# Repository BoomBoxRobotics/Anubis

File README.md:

# Anubis RC Controller Daughterboard

**A compact open-hardware support board for a DIY ESP32-S3 RC transmitter.**

Anubis is an open hardware and open firmware RC controller project built around accessible DIY parts, modern radio-control features, and a design that builders can understand, repair, modify, and improve.

This repository contains the custom daughterboard for the Anubis controller. It sits under a Hosyond 2.8 inch ESP32-S3 display board and turns the early wiring-heavy prototype into a cleaner, more repeatable hardware platform.

## Mission

The goal is simple: make a capable, repairable, hackable transmitter that is not locked behind a black box.

The first Anubis prototype used off-the-shelf modules wired together by hand: display board, power switches, regulators, analog input boards, GPIO expanders, gimbal connectors, and radio wiring. That is a great way to prove an idea, but it gets messy fast. This daughterboard pulls those support circuits onto a purpose-built PCB while leaving the Hosyond ESP32-S3 board as the main brain, display, touch interface, and firmware target.

Anubis is meant for experimentation as much as use. Builders should be able to change pin mappings, adapt connectors, swap radio hardware, and tune the firmware for their own transmitter layout.

## At A Glance

| Area | Current Direction |
| --- | --- |
| Main controller | Hosyond 2.8 inch ESP32-S3 display/dev board |
| Battery system | 2S LiPo or two 18650 cells as a 2S pack |
| Charging input | USB-C 5 V input, 500 mA to 1.5 A charge target |
| Switched outputs | `+5V_SW` and `+3V3_SW` accessory rails |
| Analog inputs | Two onboard ADS1115 ADCs, up to 8 analog channels |
| GPIO expansion | MCP23017 16-bit I2C GPIO expander |
| Radio paths | ELRS/CRSF over UART and optional ESP-NOW |
| Assembly goal | As much JLCPCB assembly as practical |
| Project status | Prototype hardware, ready for assembled-board validation |

## Core Design Goals

- Use common, hobby-accessible parts where possible.
- Keep the project open enough for community modification.
- Support modern RC workflows such as ELRS and ESP-NOW.
- Reduce hand wiring compared with the early prototype.
- Make the board practical for JLCPCB assembly.
- Keep external accessory power switchable from firmware.
- Leave room for manual wiring where real-world modules and harnesses vary.

## Hardware Overview

The daughterboard adds the support electronics around the Hosyond ESP32-S3 board:

- USB-C 5 V input for charging and power input.
- Standard 2S LiPo balance connector for the battery pack.
- Support for a 2S LiPo pack or two 18650 cells configured as a 2S pack.
- 2S battery gauge/protection circuitry based around `BQ28Z610DRZR-R1`.
- R14 high-side protection path using two JLC-available `CSD18502Q5B` N-FETs, with the charger and buck regulators fed from protected `BAT_SYS`.
- Switched 5 V rail for UART/ELRS-side accessories.
- Switched 3.3 V rail for I2C, analog, and low-voltage peripherals.
- Two Pololu mini pushbutton power switch modules for rail control.
- Two onboard ADS1115 ADC circuits for up to eight analog inputs.
- One onboard MCP23017 GPIO expander for buttons and digital expansion.
- JST and pin-header breakouts for UART, I2C, GPIO, gimbals, and accessories.
- ESD protection for external signal connections.
- Ground plane and wider routing rules for higher-current power paths.

## Power Rails

| Rail | Intended Use | Approximate Max Current |
| --- | --- | --- |
| USB-C input | 5 V charge/input source | 500 mA to 1.5 A charge target |
| `+5V_SW` | ELRS/UART-side accessory power | about 1 A |
| `+3V3_SW` | I2C, ADCs, MCP23017, gimbals, sensors | about 500 mA |

The switched rails are controlled through the two Pololu #2808 mini pushbutton power switch modules. The ESP32-S3 can shut down attached devices without relying on the attached devices to behave nicely.

## Firmware Map

The main Anubis firmware runs on the Hosyond ESP32-S3 board. Current daughterboard-aware firmware support includes:

- Touchscreen UI for transmitter settings.
- Model storage and configuration.
- Stick calibration.
- Expo, rates, trims, endpoints, failsafe, and mixing.
- ELRS/CRSF support over UART.
- ESP-NOW transmitter support.
- Dual ADS1115 support for onboard analog inputs at `0x48` and `0x49`.
- MCP23017 GPIO expander support at `0x20`.
- Battery monitoring and deep-sleep behavior.

### Pin Assignments

| Function | ESP32-S3 Pin |
| --- | --- |
| I2C SDA | GPIO16 |
| I2C SCL | GPIO15 |
| ELRS/UART TX | GPIO44 |
| ELRS/UART RX | GPIO43 |
| Battery ADC | GPIO9 |
| 5 V rail switch control | GPIO2 |
| 3.3 V rail switch control | GPIO3 |
| Deep-sleep/wake button sense | GPIO14 |
| Deep-sleep/wake button reference | GPIO21 |

GPIO2 and GPIO3 control the two Pololu rail-switch modules. GPIO14 and GPIO21 route to the two-pin deep-sleep/wake pushbutton header. UART-to-ELRS wiring can still be crossed manually if a specific module harness expects the opposite order.

### I2C Devices

| Device | Address | Role |
| --- | --- | --- |
| ADS1115 primary | `0x48` | Four gimbal/stick analog axes |
| ADS1115 auxiliary | `0x49` | Spare analog inputs |
| MCP23017 | `0x20` | GPIO expansion and active-low button/switch inputs |
| BQ25887 charger | `0x6B` | 2S charger status and pack voltage reporting |

## Control Hardware

The controller is designed around parts that are easy for hobby builders to source or substitute:

- Hosyond 2.8 inch ESP32-S3 display board as the main controller.
- RadioMaster Pocket/Zorro X5-style gimbals.
- ELRS module support through UART/CRSF.
- Optional ESP-NOW receiver support for WiFi-equipped ESP32 receivers.
- D-pad/button input through the MCP23017 GPIO expander.
- Auxiliary analog inputs through the ADS1115 circuits.

The mechanical layout fits around the Hosyond board and controller shell constraints. The Hosyond board sits above the daughterboard on standoffs, with the daughterboard occupying the surrounding and lower internal space.

## Repository Contents

| Path | Purpose |
| --- | --- |
| `Daughterboard.kicad_pro` | KiCad project file |
| `Daughterboard.kicad_sch` | Main schematic |
| `Daughterboard.kicad_pcb` | PCB layout |
| `Daughterboard.kicad_sym` | Project symbols |
| `Daughterboard.pretty/` | Custom KiCad footprints |
| `Daughterboard.net` | Exported netlist |
| `Daughterboard_pcb_bom.csv` | Human-readable PCB BOM |
| `Daughterboard_current_jlc_part_audit.csv` | JLC part audit/reference |
| `fabrication/` | Fabrication and assembly outputs |
| `daughterboard2.dxf` | Board outline reference |
| `Daughterboardv2.step` | Mechanical board reference |
| `PROJECT_CONTEXT.md` | Detailed working context for future development |

Current fabrication package:

```text
fabrication/jlcpcb_2026-07-10_r14.zip
```

Assembly files are included under:

```text
fabrication/jlcpcb_2026-07-10_r14/assembly/
```

## Manufacturing Notes

The board is being prepared for JLCPCB assembly with as many populated parts as practical. The Pololu mini pushbutton power switch modules are treated as separately installed modules. Some through-hole headers may also be hand-installed unless through-hole assembly is explicitly ordered.

Before ordering boards, always check:

- KiCad ERC and DRC reports.
- Copper clearance and board-edge clearance.
- Unrouted nets.
- Connector orientation.
- IC pin 1 orientation.
- JLCPCB part availability.
- BOM and CPL alignment in the JLCPCB preview.

Known current status from the active R14 working files:

- ERC reports no errors or warnings.
- Q1/Q2 are now JLC-available `CSD18502Q5B` FETs using project-local TI DNK/VSON-CLIP footprints.
- The R14 topology audit passes: USB-C ground, charger/system bus, high-side protection FETs, current-sense resistor, and SRP/SRN polarity all match the corrected battery-protection intent.
- The PCB has been rerouted after the Q1/Q2 footprint swap and the GND zone has been refilled.
- DRC currently reports 40 known non-connectivity items and 0 unconnected pads/items.
- JLC assembly still needs confirmed selections for `R49` and `R50`.
- Silkscreen warnings should not normally prevent fabrication.
- Copper, drill, outline, missing-net, and footprint-orientation issues should be treated as critical.

## Battery And Power Safety

This board works with lithium battery packs and charging/protection circuitry. Mistakes can damage hardware or create a safety hazard.

Do not assume a PCB revision is safe just because the schematic opens or the Gerbers generate. Review the battery path, charger configuration, protection FETs, current limits, connector polarity, and pack wiring before connecting real cells.

Use protected cells or a known-good 2S pack during testing. Current-limit the first power-up and verify rails with a meter before plugging in the Hosyond board or radio hardware.

## Project Status

This hardware is still a prototype until assembled boards are tested.

Open work includes:

- Validate the physical PCB after manufacturing.
- Confirm all connector orientations in the assembled board.
- Test the updated firmware GPIO assignments against the first assembled daughterboard.
- Verify 2S battery reporting and charger/fuel-gauge behavior on hardware.
- Confirm the auxiliary ADS1115 inputs and MCP23017 pads behave as expected with real devices attached.
- Test ELRS and ESP-NOW behavior in the finished controller.
- Document assembly steps after the first successful build.

## Contributing

Anubis is meant to be community driven. Contributions are welcome in the form of firmware changes, PCB review, mechanical improvements, documentation, testing notes, alternate part suggestions, and build reports.

If you change the hardware, include enough context for another builder to understand why the change was made. If you change the firmware, document the pin assumptions and hardware revision you tested against.

## Companion Project

The firmware and receiver-side code for the broader Anubis controller project are hosted with the main project:

```text
https://github.com/BoomBoxRobotics/Anubis
```

This daughterboard is one hardware path toward that larger goal: a capable open source RC controller that builders can actually understand, repair, and make their own.

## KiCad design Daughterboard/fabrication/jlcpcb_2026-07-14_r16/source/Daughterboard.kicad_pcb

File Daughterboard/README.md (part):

# Anubis RC Controller Daughterboard

**A compact open-hardware support board for a DIY ESP32-S3 RC transmitter.**

Anubis is an open hardware and open firmware RC controller project built around accessible DIY parts, modern radio-control features, and a design that builders can understand, repair, modify, and improve.

This repository contains the custom daughterboard for the Anubis controller. It sits under a Hosyond 2.8 inch ESP32-S3 display board and turns the early wiring-heavy prototype into a cleaner, more repeatable hardware platform.

## Mission

The goal is simple: make a capable, repairable, hackable transmitter that is not locked behind a black box.

The first Anubis prototype used off-the-shelf modules wired together by hand: display board, power switches, regulators, analog input boards, GPIO expanders, gimbal connectors, and radio wiring. That is a great way to prove an idea, but it gets messy fast. This daughterboard pulls those support circuits onto a purpose-built PCB while leaving the Hosyond ESP32-S3 board as the main brain, display, touch interface, and firmware target.

Anubis is meant for experimentation as much as use. Builders should be able to change pin mappings, adapt connectors, swap radio hardware, and tune the firmware for their own transmitter layout.

## At A Glance

| Area | Current Direction |
| --- | --- |
| Main controller | Hosyond 2.8 inch ESP32-S3 display/dev board |
| Battery system | 2S LiPo or two 18650 cells as a 2S pack |
| Charging input | USB-C 5 V input, 500 mA to 1.5 A charge target |
| Switched outputs | `+5V_SW` and `+3V3_SW` accessory rails |
| Analog inputs | Two onboard ADS1115 ADCs, up to 8 analog channels |
| GPIO expansion | MCP23017 16-bit I2C GPIO expander |
| Radio paths | ELRS/CRSF over UART and optional ESP-NOW |
| Assembly goal | As much JLCPCB assembly as practical |
| Project status | Prototype hardware, ready for assembled-board validation |

## Core Design Goals

- Use common, hobby-accessible parts where possible.
- Keep the project open enough for community modification.
- Support modern RC workflows such as ELRS and ESP-NOW.
- Reduce hand wiring compared with the early prototype.
- Make the board practical for JLCPCB assembly.
- Keep external accessory power switchable from firmware.
- Leave room for manual wiring where real-world modules and harnesses vary.

## Hardware Overview

The daughterboard adds the support electronics around the Hosyond ESP32-S3 board:

- USB-C 5 V input for charging and power input.
- Standard 2S LiPo balance connector for the battery pack.
- Support for a 2S LiPo pack or two 18650 cells configured as a 2S pack.
- 2S battery gauge/protection circuitry based around `BQ28Z610DRZR-R1`.
- R14 high-side protection path using two JLC-available `CSD18502Q5B` N-FETs, with the charger and buck regulators fed from protected `BAT_SYS`.
- Switched 5 V rail for UART/ELRS-side accessories.
- Switched 3.3 V rail for I2C, analog, and low-voltage peripherals.
- Two Pololu mini pushbutton power switch modules for rail control.
- Two onboard ADS1115 ADC circuits for up to eight analog inputs.
- One onboard MCP23017 GPIO expander for buttons and digital expansion.
- JST and pin-header breakouts for UART, I2C, GPIO, gimbals, and accessories.
- ESD protection for external signal connections.
- Ground plane and wider routing rules for higher-current power paths.

## Power Rails

| Rail | Intended Use | Approximate Max Current |
| --- | --- | --- |
| USB-C input | 5 V charge/input source | 500 mA to 1.5 A charge target |
| `+5V_SW` | ELRS/UART-side accessory power | about 1 A |
| `+3V3_SW` | I2C, ADCs, MCP23017, gimbals, sensors | about 500 mA |

The switched rails are controlled through the two Pololu #2808 mini pushbutton power switch modules. The ESP32-S3 can shut down attached devices without relying on the attached devices to behave nicely.

## Firmware Map

The main Anubis firmware runs on the Hosyond ESP32-S3 board. Current daughterboard-aware firmware support includes:

- Touchscreen UI for transmitter settings.
- Model storage and configuration.
- Stick calibration.
- Expo, rates, trims, endpoints, failsafe, and mixing.
- ELRS/CRSF support over UART.
- ESP-NOW transmitter support.
- Dual ADS1115 support for onboard analog inputs at `0x48` and `0x49`.
- MCP23017 GPIO expander support at `0x20`.
- Battery monitoring and deep-sleep behavior.

### Pin Assignments

| Function | ESP32-S3 Pin |
| --- | --- |
| I2C SDA | GPIO16 |
| I2C SCL | GPIO15 |
| ELRS/UART TX | GPIO44 |
| ELRS/UART RX | GPIO43 |
| Battery ADC | GPIO9 |
| 5 V rail switch control | GPIO2 |
| 3.3 V rail switch control | GPIO3 |
| Deep-sleep/wake button sense | GPIO14 |
| Deep-sleep/wake button reference | GPIO21 |

GPIO2 and GPIO3 control the two Pololu rail-switch modules. GPIO14 and GPIO21 route to the two-pin deep-sleep/wake pushbutton header. UART-to-ELRS wiring can still be crossed manually if a specific module harness expects the opposite order.

### I2C Devices

| Device | Address | Role |
| --- | --- | --- |
| ADS1115 primary | `0x48` | Four gimbal/stick analog axes |
| ADS1115 auxiliary | `0x49` | Spare analog inputs |
| MCP23017 | `0x20` | GPIO expansion and active-low button/switch inputs |
| BQ25887 charger | `0x6B` | 2S charger status and pack voltage reporting |

## Board Connection Reference

The following tables describe the designators and nets on the R14 PCB. Pin numbers are the KiCad footprint pin numbers and should be checked against connector orientation and pin-1 markings before making a cable.

### Electrical Test Pads

| Pad | Net | Signal source or intended measurement |
| --- | --- | --- |
| `TP1` | `USB_VBUS` | USB-C `J1` VBUS, before input fuse `F1` |
| `TP2` | `CHG_IN` | Fused USB input after `F1`; charger `U1` pin 23 |
| `TP3` | `BAT_SYS` | Protected battery/system bus feeding charger `U1` BAT pins and the 5 V/3.3 V regulators |
| `TP4` | `CELL_MID` | 2S pack midpoint from `J7` pin 2; charger `U1` pin 9 sense connection |
| `TP5` | `BAT_SYS` | Second protected battery/system-bus test point; electrically the same as `TP3` |
| `TP6` | `+5V` | Unswitched 5 V regulator output after `L1`, before Pololu switch `SW1` |
| `TP7` | `+3V3` | Unswitched 3.3 V regulator output after `L2`, before Pololu switch `SW2` |
| `TP9` | `+3V3_SW` | Switched 3.3 V output from `SW2` |
| `TP10` | `CHG_STAT` | Charger `U1` pin 2 charge-status output; also drives status LED `D2` |
| `TP11` | `PG_STAT` | Charger `U1` pin 1 power-good output; also drives status LED `D3` |
| `TP12` | `BATT_RAW_N` | Raw pack negative from `J7` pin 1, on the battery side of current-sense resistor `R46` |
| `TP13` | `BATT_RAW_P` | Raw pack positive from `J7` pin 3 |
| `TP14` | `GND` | System ground, on the system side of current-sense resistor `R46` |
| `TP15` | `AIN4` | Auxiliary ADC `U6` (`0x49`) AIN0, pin 4 |
| `TP16` | `AIN5` | Auxiliary ADC `U6` (`0x49`) AIN1, pin 5 |
| `TP17` | `AIN6` | Auxiliary ADC `U6` (`0x49`) AIN2, pin 6 |
| `TP18` | `AIN7` | Auxiliary ADC `U6` (`0x49`) AIN3, pin 7 |

`TP8` is not fitted on the R14 PCB. Use `J30` or `J4` pin 1 to access `+5V_SW`. Also note that `BATT_RAW_N` and `GND` are separated by the 2 mOhm current-sense resistor; do not treat `TP12` and `TP14` as interchangeable measurement points.

### Hosyond Manual Solder Pads

These pads replace the original `J3` connector so individual wires from the Hosyond board can be soldered directly to the daughterboard.

| Pad | Net | Hosyond/source mapping |
| --- | --- | --- |
| `J30` | `+5V_SW` | Switched 5 V output from `SW1`; also available at `J4` pin 1 |
| `J31` | `UART_TX` | Hosyond ESP32-S3 GPIO44; routed to `J4` pin 3 |
| `J32` | `UART_RX` | Hosyond ESP32-S3 GPIO43; routed to `J4` pin 4 |
| `J33` | `I2C_SDA` | Hosyond ESP32-S3 GPIO16; shared daughterboard I2C data bus |
| `J34` | `I2C_SCL` | Hosyond ESP32-S3 GPIO15; shared daughterboard I2C clock bus |
| `J35` | `GPIO2` | Hosyond ESP32-S3 GPIO2; drives `SW1` 5 V control through `R17` |
| `J36` | `GPIO3` | Hosyond ESP32-S3 GPIO3; drives `SW2` 3.3 V control through `R18` |
| `J37` | `GPIO14` | Hosyond ESP32-S3 GPIO14; routed to wake-button header `J6` pin 1 |
| `J38` | `GPIO21` | Hosyond ESP32-S3 GPIO21; routed to wake-button header `J6` pin 2 |
| `J39` | `GND` | Daughterboard system ground |

### MCP23017 Manual Solder Pads

The `EXP_*` GPIO pads are on the protected external side of a 100 ohm series resistor and an ESD array. `U7` is the MCP23017 at I2C address `0x20`.

| Pad | Net | Source |
| --- | --- | --- |
| `J91` | `EXP_GPA0` | `U7` GPA0 pin 21 through `R23`; ESD `D4` |
| `J92` | `EXP_GPA1` | `U7` GPA1 pin 22 through `R24`; ESD `D4` |
| `J93` | `EXP_GPA2` | `U7` GPA2 pin 23 through `R25`; ESD `D4` |
| `J94` | `EXP_GPA3` | `U7` GPA3 pin 24 through `R26`; ESD `D4` |
| `J95` | `EXP_GPA4` | `U7` GPA4 pin 25 through `R27`; ESD `D5` |
| `J96` | `EXP_GPA5` | `U7` GPA5 pin 26 through `R28`; ESD `D5` |
| `J97` | `EXP_GPA6` | `U7` GPA6 pin 27 through `R29`; ESD `D5` |
| `J98` | `EXP_GPA7` | `U7` GPA7 pin 28 through `R30`; ESD `D5` |
| `J99` | `EXP_GPB0` | `U7` GPB0 pin 1 through `R31`; ESD `D6` |
| `J910` | `EXP_GPB1` | `U7` GPB1 pin 2 through `R32`; ESD `D6` |
| `J911` | `EXP_GPB2` | `U7` GPB2 pin 3 through `R33`; ESD `D6` |
| `J912` | `EXP_GPB3` | `U7` GPB3 pin 4 through `R34`; ESD `D6` |
| `J913` | `EXP_GPB4` | `U7` GPB4 pin 5 through `R35`; ESD `D7` |
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
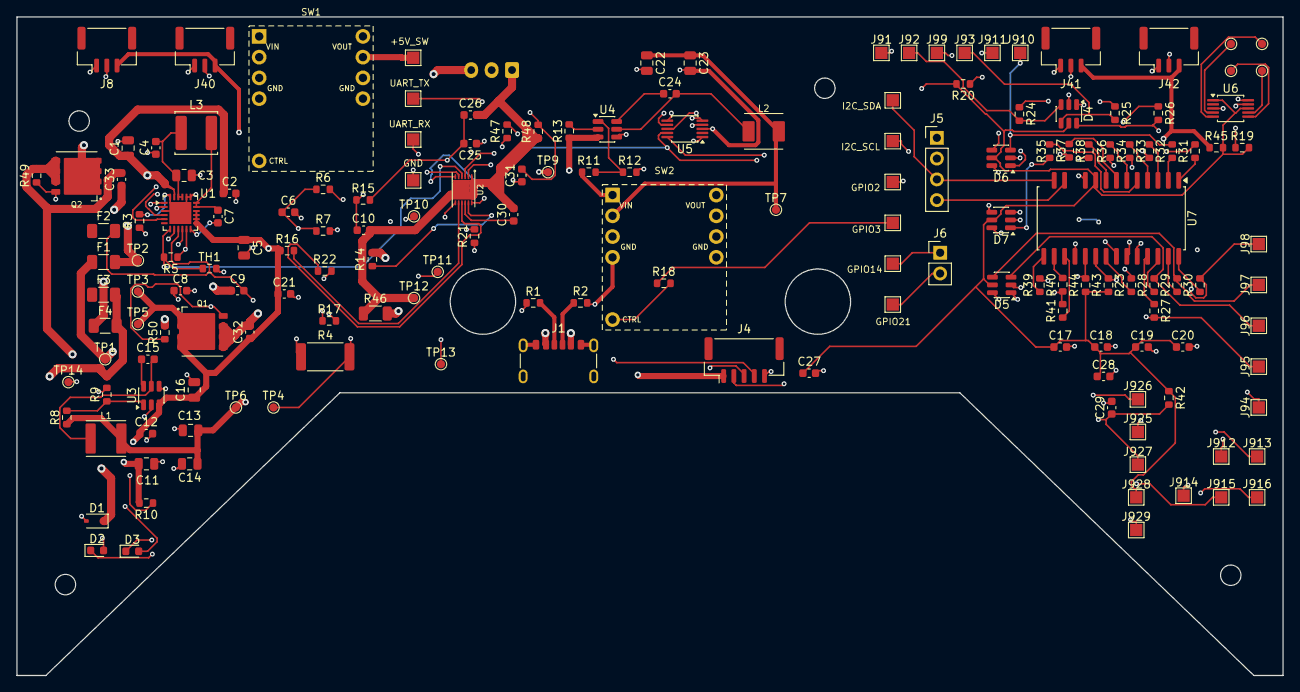
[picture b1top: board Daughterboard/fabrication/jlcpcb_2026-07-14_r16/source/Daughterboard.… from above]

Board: 4 copper layers, 155.0 x 80.6 mm, 166 parts (0 on the bottom side), 101 nets.

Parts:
C1: 10uF 10V X5R; C_0805_2012Metric
C2, C17, C19, C27, C29: 100nF 10V X7R; C_0603_1608Metric
C3, C5, C13, C14, C22, C23: 22uF 16V X5R; C_0805_2012Metric
C4, C7, C9, C10, C12, C15, C21, C24, C25, C26, C31: 100nF 16V X7R; C_0603_1608Metric
C6: 4.7uF 6.3V X5R; C_0603_1608Metric
C8: 100nF 10V X7R DNP; C_0603_1608Metric
C11, C16: 10uF 16V X5R; C_0805_2012Metric
C18, C20, C28: 1uF 10V X5R; C_0603_1608Metric
C30: 2.2uF 10V X5R; C_0603_1608Metric
C32, C33: 100nF 25V X7R; C_0603_1608Metric
D1: PESD5V0S1BA 5V VBUS TVS; D_SOD-323
D2: LED green; LED_0603_1608Metric
D3: LED blue; LED_0603_1608Metric
D4, D5, D6, D7: SRV05-4.TCT / C13612 4ch ESD; SOT-23-6
F1: BSMD1206-200-16V 2A hold polyfuse; Fuse_1206_3216Metric
F2: BSMD1206-200-16V cell1 PTC; Fuse_1206_3216Metric
F3: BSMD1206-200-16V cell2 PTC; Fuse_1206_3216Metric
F4: BSMD1206-200-16V system fuse; Fuse_1206_3216Metric
J1: USB-C 5V Sink; USB_C_Receptacle_GCT_USB4125-xx-x_6P_TopMnt_Horizontal
J4: BM05B-GHS-TBT UART JST-GH top-entry 1.25mm; JST_GH_BM05B-GHS-TBT_1x05-1MP_P1.25mm_Vertical
J5: I2C 2.54mm through-hole male header; PinHeader_1x04_P2.54mm_Vertical
J6: Deep sleep 2.54mm through-hole header; PinHeader_1x02_P2.54mm_Vertical
J7: 2S balance input JST-XH side-entry; JST_XH_S3B-XH-A_1x03_P2.50mm_Horizontal
J8: Left gimbal A JST-GH 1.25mm; JST_GH_BM03B-GHS-TBT_1x03-1MP_P1.25mm_Vertical
J30: J3P Hosyond +5V_SW solder pad; TestPoint_Pad_1.5x1.5mm
J31: J3A Hosyond UART_TX solder pad; TestPoint_Pad_1.5x1.5mm
J32: J3B Hosyond UART_RX solder pad; TestPoint_Pad_1.5x1.5mm
J33: J3C Hosyond I2C_SDA solder pad; TestPoint_Pad_1.5x1.5mm
J34: J3D Hosyond I2C_SCL solder pad; TestPoint_Pad_1.5x1.5mm
J35: J3E Hosyond GPIO2 solder pad; TestPoint_Pad_1.5x1.5mm
J36: J3F Hosyond GPIO3 solder pad; TestPoint_Pad_1.5x1.5mm
J37: J3G Hosyond GPIO14 solder pad; TestPoint_Pad_1.5x1.5mm
J38: J3H Hosyond GPIO21 solder pad; TestPoint_Pad_1.5x1.5mm
J39: J3I Hosyond GND solder pad; TestPoint_Pad_1.5x1.5mm
J40: Left gimbal B JST-GH 1.25mm; JST_GH_BM03B-GHS-TBT_1x03-1MP_P1.25mm_Vertical
J41: Right gimbal A JST-GH 1.25mm; JST_GH_BM03B-GHS-TBT_1x03-1MP_P1.25mm_Vertical
J42: Right gimbal B JST-GH 1.25mm; JST_GH_BM03B-GHS-TBT_1x03-1MP_P1.25mm_Vertical
J91: MCP23017 GPA0 solder pad; TestPoint_Pad_1.5x1.5mm
J92: MCP23017 GPA1 solder pad; TestPoint_Pad_1.5x1.5mm
J93: MCP23017 GPA2 solder pad; TestPoint_Pad_1.5x1.5mm
J94: MCP23017 GPA3 solder pad; TestPoint_Pad_1.5x1.5mm
J95: MCP23017 GPA4 solder pad; TestPoint_Pad_1.5x1.5mm
J96: MCP23017 GPA5 solder pad; TestPoint_Pad_1.5x1.5mm
J97: MCP23017 GPA6 solder pad; TestPoint_Pad_1.5x1.5mm
J98: MCP23017 GPA7 solder pad; TestPoint_Pad_1.5x1.5mm
J99: MCP23017 GPB0 solder pad; TestPoint_Pad_1.5x1.5mm
J910: MCP23017 GPB1 solder pad; TestPoint_Pad_1.5x1.5mm
J911: MCP23017 GPB2 solder pad; TestPoint_Pad_1.5x1.5mm
J912: MCP23017 GPB3 solder pad; TestPoint_Pad_1.5x1.5mm
J913: MCP23017 GPB4 solder pad; TestPoint_Pad_1.5x1.5mm
J914: MCP23017 GPB5 solder pad; TestPoint_Pad_1.5x1.5mm
J915: MCP23017 GPB6 solder pad; TestPoint_Pad_1.5x1.5mm
J916: MCP23017 GPB7 solder pad; TestPoint_Pad_1.5x1.5mm
J925: MCP23017 INTA solder pad; TestPoint_Pad_1.5x1.5mm
J926: MCP23017 INTB solder pad; TestPoint_Pad_1.5x1.5mm
J927: MCP23017 RESET solder pad; TestPoint_Pad_1.5x1.5mm
J928: MCP23017 +3V3_SW solder pad; TestPoint_Pad_1.5x1.5mm
J929: MCP23017 GND solder pad; TestPoint_Pad_1.5x1.5mm
L1: 4.7uH >=3A sat; CENKER_CKST0402_4.6x4.1mm
L2: 4.7uH >=2A sat; KOHERelec_MDA4020_4.45x4.1mm
L3: ANR5040T1R0M 1uH; L_APV_ANR5040
Q1: CSD18502Q5B charge FET; CSD18502Q5B_DNK0008A_VSON-CLIP_5x6mm
Q2: CSD18502Q5B discharge FET; CSD18502Q5B_DNK0008A_VSON-CLIP_5x6mm
R1, R2: 5.1k 1%; R_0603_1608Metric
R3: 806R 1% ILIM; R_0603_1608Metric
R4: 43R 1W CBSET; R_2512_6332Metric
R5: 10k 1%; R_0603_1608Metric
R6, R7: 2.2k; R_0603_1608Metric
R8: 523k 1%; R_0603_1608Metric
R9, R12: 100k 1%; R_0603_1608Metric
R10, R13: 100k; R_0603_1608Metric
R11: 316k 1%; R_0603_1608Metric
R14, R15: 470R 1%; R_0603_1608Metric
R16, R21, R22, R23, R24, R25, R26, R27, R28, R29, R30, R31, R32, R33, R34, R35, R36, R37, R38, R47, R48: 100R; R_0603_1608Metric
R17, R18: 330R; R_0603_1608Metric
R19, R20: 4.7k; R_0603_1608Metric
R39, R40, R41, R45: 0R; R_0603_1608Metric
R42, R43, R44: 10k; R_0603_1608Metric
R46: 2mR 1% 50ppm; R_1206_3216Metric
R49, R50: 10M; R_0603_1608Metric
SW1: Pololu #2808 5V switch; Pololu_2808_Raised_Header
SW2: Pololu #2808 3V3 switch; Pololu_2808_Raised_Header
TH1: NCP18XH103F03RB 10k NTC; R_0603_1608Metric
TP1: USB_VBUS test pad; TestPoint_Pad_D1.0mm
TP2: CHG_IN test pad; TestPoint_Pad_D1.0mm
TP3, TP5: BAT_SYS test pad; TestPoint_Pad_D1.0mm
TP4: CELL_MID test pad; TestPoint_Pad_D1.0mm
TP6: +5V test pad; TestPoint_Pad_D1.0mm
TP7: +3V3 test pad; TestPoint_Pad_D1.0mm
TP9: +3V3_SW test pad; TestPoint_Pad_D1.0mm
TP10: CHG_STAT test pad; TestPoint_Pad_D1.0mm
TP11: PG_STAT test pad; TestPoint_Pad_D1.0mm
TP12: BATT_RAW_N test pad; TestPoint_Pad_D1.0mm
TP13: BATT_RAW_P test pad; TestPoint_Pad_D1.0mm
TP14: GND test pad; TestPoint_Pad_D1.0mm
TP15: AIN4 test pad; TestPoint_Pad_D1.0mm
TP16: AIN5 test pad; TestPoint_Pad_D1.0mm
TP17: AIN6 test pad; TestPoint_Pad_D1.0mm
TP18: AIN7 test pad; TestPoint_Pad_D1.0mm
U1: BQ25887RGER 2S charger; Texas_RGE0024H_VQFN-24-1EP_4x4mm_P0.5mm_EP2.7x2.7mm
U2: BQ28Z610DRZR-R1; TI_DRZ0012A_VSON-12_4x2.5mm_P0.4mm
U3: AP63200WU-7 5V Buck; TSOT-23-6
U4: AP63200WU-7 3V3 Buck; TSOT-23-6
U5: ADS1115IDGSR 0x48; TSSOP-10_3x3mm_P0.5mm
U6: ADS1115IDGSR 0x49; TSSOP-10_3x3mm_P0.5mm
U7: MCP23017-E/SO; SOIC-28W_7.5x17.9mm_P1.27mm_NoPads11_14

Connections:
+3V3: C22.1, C23.1, L2.2, R11.1, SW2.1, TP7.1
+3V3_SW: J5.1, J8.3, J40.3, J41.3, J42.3, R45.1, SW2.2, TP9.1
+3V3_SW_LOGIC: C17.1, C18.1, C19.1, C20.1, C27.1, C28.1, D4.5, D5.5, D6.5, D7.5, J928.1, R19.2, R20.2, R42.1, R43.1, R44.1, R45.2, U5.8, U6.1, U6.8, U7.9
+5V: C13.1, C14.1, L1.2, R8.1, SW1.1, TP6.1
+5V_SW: J4.1, J30.1, SW1.2
AIN0: J8.2, U5.4
AIN1: J40.2, U5.5
AIN2: J41.2, U5.6
AIN3: J42.2, U5.7
AIN4: TP15.1, U6.4
AIN5: TP16.1, U6.5
AIN6: TP17.1, U6.6
AIN7: TP18.1, U6.7
BATT_RAW_N: C10.2, C26.2, C30.2, J7.1, R46.1, R48.1, TP12.1, U2.1, U2.13
BATT_RAW_P: C9.1, F3.2, F4.2, J7.3, R14.1, TP13.1
BAT_SYS: C5.1, C11.1, C12.1, C16.1, C21.1, C32.1, Q1.5, Q1.6, Q1.7, Q1.8, R10.2, R13.2, R16.1, TP3.1, TP5.1, U1.13, U1.14, U1.15, U1.16, U3.3, U4.3
BQ_CHG: R22.1, U2.9
BQ_DSG: R21.1, U2.7
BQ_PACK: R16.2, U2.8
BQ_PBI: C30.1, U2.10
BQ_SRN: C31.1, R47.2, U2.2
BQ_SRP: C31.2, R48.2, U2.3
BST_3V3: C24.1, U4.6
BST_5V: C15.1, U3.6
BTST: C7.1, U1.12
CBSET: C8.1, R4.1, U1.10
CC1: J1.A5, R1.1
CC2: J1.B5, R2.1
CELL_MID: C9.2, C10.1, F2.2, J7.2, R4.2, R15.1, TP4.1, U1.9
CHG_IN: C1.1, C2.1, D1.1, F1.2, TP2.1, U1.23
CHG_STAT: D2.2, TP10.1, U1.2
CHG_SW: C7.2, L3.2, U1.17, U1.18
CO_GATE: Q1.4, R22.2, R50.1
CTRL_3V3_SW: R18.2, SW2.4
CTRL_5V_SW: R17.2, SW1.4
DO_GATE: Q2.4, R21.2, R49.1
EN_3V3: R13.1, U4.2
EN_5V: R10.1, U3.2
EXP_GPA0: D4.1, J91.1, R23.2
EXP_GPA1: D4.3, J92.1, R24.2
EXP_GPA2: D4.4, J93.1, R25.2
EXP_GPA3: D4.6, J94.1, R26.2
EXP_GPA4: D5.1, J95.1, R27.2
EXP_GPA5: D5.3, J96.1, R28.2
EXP_GPA6: D5.4, J97.1, R29.2
EXP_GPA7: D5.6, J98.1, R30.2
EXP_GPB0: D6.1, J99.1, R31.2
EXP_GPB1: D6.3, J910.1, R32.2
EXP_GPB2: D6.4, J911.1, R33.2
EXP_GPB3: D6.6, J912.1, R34.2
EXP_GPB4: D7.1, J913.1, R35.2
EXP_GPB5: D7.3, J914.1, R36.2
EXP_GPB6: D7.4, J915.1, R37.2
EXP_GPB7: D7.6, J916.1, R38.2
FB_3V3: R11.2, R12.1, U4.1
FB_5V: R8.2, R9.1, U3.1
FET_BATT_P: C33.1, F4.1, Q2.5, Q2.6, Q2.7, Q2.8
FET_SRC_COMMON: C32.2, C33.2, Q1.1, Q1.2, Q1.3, Q2.1, Q2.2, Q2.3, R49.2, R50.2
GND: C1.2, C2.2, C3.2, C4.2, C5.2, C6.2, C8.2, C11.2, C12.2, C13.2, C14.2, C16.2, C17.2, C18.2, C19.2, C20.2, C21.2, C22.2, C23.2, C27.2, C28.2, C29.2, D1.2, D4.2, D5.2, D6.2, D7.2, J1.A12, J1.B12, J1.SH, J4.2, J4.5, J5.2, J8.1, J39.1, J40.1, J41.1, J42.1, J929.1, R1.2, R2.2, R3.2, R9.2, R12.2, R39.2, R40.2, R41.2, R46.2, R47.1, SW1.3, SW2.3, TH1.2, TP14.1, U1.3, U1.19, U1.20, U1.24, U1.25, U3.4, U4.4, U5.1, U5.3, U6.3, U7.10
GPIO2: J35.1, R17.1
GPIO3: J36.1, R18.1
GPIO14: J6.1, J37.1
GPIO21: J6.2, J38.1
I2C_SCL: J5.4, J34.1, R20.1, U1.5, U2.5, U5.10, U6.10, U7.12
I2C_SDA: J5.3, J33.1, R19.1, U1.4, U2.6, U5.9, U6.9, U7.13
ILIM: R3.1, U1.8
LED_CHG_A: D2.1, R6.2
LED_PGOOD_A: D3.1, R7.2
MCP_A0: R39.1, U7.15
MCP_A1: R40.1, U7.16
MCP_A2: R41.1, U7.17
MCP_GPA0: R23.1, U7.21
MCP_GPA1: R24.1, U7.22
MCP_GPA2: R25.1, U7.23
MCP_GPA3: R26.1, U7.24
MCP_GPA4: R27.1, U7.25
MCP_GPA5: R28.1, U7.26
MCP_GPA6: R29.1, U7.27
MCP_GPA7: R30.1, U7.28
MCP_GPB0: R31.1, U7.1
MCP_GPB1: R32.1, U7.2
MCP_GPB2: R33.1, U7.3
MCP_GPB3: R34.1, U7.4
MCP_GPB4: R35.1, U7.5
MCP_GPB5: R36.1, U7.6
MCP_GPB6: R37.1, U7.7
MCP_GPB7: R38.1, U7.8
MCP_INTA: J925.1, R43.2, U7.20
MCP_INTB: J926.1, R44.2, U7.19
MCP_RESET: C29.1, J927.1, R42.2, U7.18
PG_STAT: D3.2, TP11.1, U1.1
PMID: C3.1, C4.1, L3.1, U1.21, U1.22
PROT_VC: C25.2, C26.1, R15.2, U2.12
PROT_VDD: C25.1, R14.2, U2.11
REGN: C6.1, R5.1, R6.1, R7.1, U1.11
SW_3V3: C24.2, L2.1, U4.5
SW_5V: C15.2, L1.1, U3.5
TS: R5.2, TH1.1, U1.7, U2.4
UART_RX: J4.4, J32.1
UART_TX: J4.3, J31.1
USB_VBUS: F1.1, J1.A9, J1.B9, TP1.1

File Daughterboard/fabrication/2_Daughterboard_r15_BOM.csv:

"Comment","Designator","Footprint","LCSC Part #","Quantity"
"10uF 10V X5R","C1","Capacitor_SMD:C_0805_2012Metric","C440198","1"
"100nF 10V X7R","C2","Capacitor_SMD:C_0603_1608Metric","C14663","1"
"22uF 16V X5R","C3","Capacitor_SMD:C_0805_2012Metric","C45783","1"
"100nF 16V X7R","C4","Capacitor_SMD:C_0603_1608Metric","C14663","1"
"22uF 16V X5R","C5","Capacitor_SMD:C_0805_2012Metric","C45783","1"
"4.7uF 6.3V X5R","C6","Capacitor_SMD:C_0603_1608Metric","C19666","1"
"100nF 16V X7R","C7","Capacitor_SMD:C_0603_1608Metric","C14663","1"
"100nF 16V X7R","C9","Capacitor_SMD:C_0603_1608Metric","C14663","1"
"100nF 16V X7R","C10","Capacitor_SMD:C_0603_1608Metric","C14663","1"
"10uF 16V X5R","C11","Capacitor_SMD:C_0805_2012Metric","C440198","1"
"100nF 16V X7R","C12","Capacitor_SMD:C_0603_1608Metric","C14663","1"
"22uF 10V X5R","C13","Capacitor_SMD:C_0805_2012Metric","C45783","1"
"22uF 10V X5R","C14","Capacitor_SMD:C_0805_2012Metric","C45783","1"
"100nF 16V X7R","C15","Capacitor_SMD:C_0603_1608Metric","C14663","1"
"10uF 16V X5R","C16","Capacitor_SMD:C_0805_2012Metric","C440198","1"
"100nF 10V X7R","C17","Capacitor_SMD:C_0603_1608Metric","C14663","1"
"1uF 10V X5R","C18","Capacitor_SMD:C_0603_1608Metric","C15849","1"
"100nF 10V X7R","C19","Capacitor_SMD:C_0603_1608Metric","C14663","1"
"1uF 10V X5R","C20","Capacitor_SMD:C_0603_1608Metric","C15849","1"
"100nF 16V X7R","C21","Capacitor_SMD:C_0603_1608Metric","C14663","1"
"22uF 10V X5R","C22","Capacitor_SMD:C_0805_2012Metric","C45783","1"
"22uF 10V X5R","C23","Capacitor_SMD:C_0805_2012Metric","C45783","1"
"100nF 16V X7R","C24","Capacitor_SMD:C_0603_1608Metric","C14663","1"
"100nF 16V X7R","C25","Capacitor_SMD:C_0603_1608Metric","C14663","1"
"100nF 16V X7R","C26","Capacitor_SMD:C_0603_1608Metric","C14663","1"
"100nF 10V X7R","C27","Capacitor_SMD:C_0603_1608Metric","C14663","1"
"1uF 10V X5R","C28","Capacitor_SMD:C_0603_1608Metric","C15849","1"
"100nF 10V X7R","C29","Capacitor_SMD:C_0603_1608Metric","C14663","1"
"2.2uF 10V X5R","C30","Capacitor_SMD:C_0603_1608Metric","C23630","1"
"100nF 16V X7R","C31","Capacitor_SMD:C_0603_1608Metric","C14663","1"
"100nF 25V X7R","C32","Capacitor_SMD:C_0603_1608Metric","C14663","1"
"100nF 25V X7R","C33","Capacitor_SMD:C_0603_1608Metric","C14663","1"
"5V VBUS TVS","D1","Diode_SMD:D_SOD-323","C2827694","1"
"LED green","D2","LED_SMD:LED_0603_1608Metric","C125093","1"
"LED blue","D3","LED_SMD:LED_0603_1608Metric","C99290","1"
"4ch 3.3V GPIO TVS array TBD","D4","Daughterboard:SOT-23-6_NoPad6","C13612","1"
"4ch 3.3V GPIO TVS array TBD","D5","Daughterboard:SOT-23-6_NoPad6","C13612","1"
"4ch 3.3V GPIO TVS array TBD","D6","Daughterboard:SOT-23-6_NoPad6","C13612","1"
"4ch 3.3V GPIO TVS array TBD","D7","Daughterboard:SOT-23-6_NoPad6","C13612","1"
"2A hold polyfuse","F1","Fuse:Fuse_1206_3216Metric","C2685749","1"
"PTC/fuse cell1","F2","Fuse:Fuse_1206_3216Metric","C2685749","1"
"PTC/fuse cell2","F3","Fuse:Fuse_1206_3216Metric","C2685749","1"
"2A battery path fuse","F4","Fuse:Fuse_1206_3216Metric","C2685749","1"
"USB-C 5V Sink","J1","Connector_USB:USB_C_Receptacle_GCT_USB4125-xx-x_6P_TopMnt_Horizontal","C3151650","1"
"UART JST-GH 1.25mm","J4","Connector_JST:JST_GH_SM05B-GHS-TB_1x05-1MP_P1.25mm_Horizontal","C189891","1"
"2S balance input JST-XH side-entry","J7","Connector_JST:JST_XH_S3B-XH-A_1x03_P2.50mm_Horizontal","C157928","1"
"Left gimbal A JST-GH 1.25mm","J8","Connector_JST:JST_GH_BM03B-GHS-TBT_1x03-1MP_P1.25mm_Vertical","C161691","1"
"Left gimbal B JST-GH 1.25mm","J40","Connector_JST:JST_GH_BM03B-GHS-TBT_1x03-1MP_P1.25mm_Vertical","C161691","1"
"Right gimbal A JST-GH 1.25mm","J41","Connector_JST:JST_GH_BM03B-GHS-TBT_1x03-1MP_P1.25mm_Vertical","C161691","1"
"Right gimbal B JST-GH 1.25mm","J42","Connector_JST:JST_GH_BM03B-GHS-TBT_1x03-1MP_P1.25mm_Vertical","C161691","1"
"4.7uH >=3A sat","L1","Inductor_SMD:L_APV_ANR4020","C3002596","1"
"4.7uH >=2A sat","L2","Inductor_SMD:L_APV_ANR4020","C2847471","1"
"1uH >=4A sat","L3","Inductor_SMD:L_APV_ANR5040","C7427125","1"
"CSD18502Q5B charge FET","Q1","Daughterboard:CSD18502Q5B_DNK0008A_VSON-CLIP_5x6mm","C473915","1"
"CSD18502Q5B discharge FET","Q2","Daughterboard:CSD18502Q5B_DNK0008A_VSON-CLIP_5x6mm","C473915","1"
"5.1k 1%","R1","Resistor_SMD:R_0603_1608Metric","C2907044","1"
"5.1k 1%","R2","Resistor_SMD:R_0603_1608Metric","C2907044","1"
"806R 1% TBD","R3","Resistor_SMD:R_0603_1608Metric","C2692785","1"
"TBD 1%","R4","Resistor_SMD:R_0603_1608Metric","C38957","1"
"10k 1%","R5","Resistor_SMD:R_0603_1608Metric","C5713432","1"
"2.2k","R6","Resistor_SMD:R_0603_1608Metric","C4190","1"
"2.2k","R7","Resistor_SMD:R_0603_1608Metric","C4190","1"
"523k 1%","R8","Resistor_SMD:R_0603_1608Metric","C861460","1"
"100k 1%","R9","Resistor_SMD:R_0603_1608Metric","C269699","1"
"100k","R10","Resistor_SMD:R_0603_1608Metric","C25803","1"
"316k 1%","R11","Resistor_SMD:R_0603_1608Metric","C2998125","1"
"100k 1%","R12","Resistor_SMD:R_0603_1608Metric","C269699","1"
"100k","R13","Resistor_SMD:R_0603_1608Metric","C25803","1"
"470R 1%","R14","Resistor_SMD:R_0603_1608Metric","C844564","1"
"470R 1%","R15","Resistor_SMD:R_0603_1608Metric","C844564","1"
"100R","R16","Resistor_SMD:R_0603_1608Metric","C22775","1"
"330R","R17","Resistor_SMD:R_0603_1608Metric","C23138","1"
"330R","R18","Resistor_SMD:R_0603_1608Metric","C23138","1"
"4.7k","R19","Resistor_SMD:R_0603_1608Metric","C23162","1"
"4.7k","R20","Resistor_SMD:R_0603_1608Metric","C23162","1"
"100R","R21","Resistor_SMD:R_0603_1608Metric","C22775","1"
"100R","R22","Resistor_SMD:R_0603_1608Metric","C22775","1"
"100R","R23","Resistor_SMD:R_0603_1608Metric","C22775","1"
"100R","R24","Resistor_SMD:R_0603_1608Metric","C22775","1"
"100R","R25","Resistor_SMD:R_0603_1608Metric","C22775","1"
"100R","R26","Resistor_SMD:R_0603_1608Metric","C22775","1"
"100R","R27","Resistor_SMD:R_0603_1608Metric","C22775","1"
"100R","R28","Resistor_SMD:R_0603_1608Metric","C22775","1"
"100R","R29","Resistor_SMD:R_0603_1608Metric","C22775","1"
"100R","R30","Resistor_SMD:R_0603_1608Metric","C22775","1"
"100R","R31","Resistor_SMD:R_0603_1608Metric","C22775","1"
"100R","R32","Resistor_SMD:R_0603_1608Metric","C22775","1"
"100R","R33","Resistor_SMD:R_0603_1608Metric","C22775","1"
"100R","R34","Resistor_SMD:R_0603_1608Metric","C22775","1"
"100R","R35","Resistor_SMD:R_0603_1608Metric","C22775","1"
"100R","R36","Resistor_SMD:R_0603_1608Metric","C22775","1"
"100R","R37","Resistor_SMD:R_0603_1608Metric","C22775","1"
"100R","R38","Resistor_SMD:R_0603_1608Metric","C22775","1"
"0R","R39","Resistor_SMD:R_0603_1608Metric","C21189","1"
"0R","R40","Resistor_SMD:R_0603_1608Metric","C21189","1"
"0R","R41","Resistor_SMD:R_0603_1608Metric","C21189","1"
"10k","R42","Resistor_SMD:R_0603_1608Metric","C177644","1"
"10k","R43","Resistor_SMD:R_0603_1608Metric","C177644","1"
"10k","R44","Resistor_SMD:R_0603_1608Metric","C177644","1"
"0R","R45","Resistor_SMD:R_0603_1608Metric","C21189","1"
"2mR 1% 50ppm","R46","Resistor_SMD:R_1206_3216Metric","C2904210","1"
"100R","R47","Resistor_SMD:R_0603_1608Metric","C22775","1"
"100R","R48","Resistor_SMD:R_0603_1608Metric","C22775","1"
"10k NTC","TH1","Resistor_SMD:R_0603_1608Metric","C13564","1"
"BQ25887RGE 2S charger","U1","Package_DFN_QFN:Texas_RGE0024H_VQFN-24-1EP_4x4mm_P0.5mm_EP2.7x2.7mm","C2761614","1"
"BQ28Z610DRZR-R1","U2","Daughterboard:BQ28Z610_DRZ0012A_12SON_2.5x4mm_P0.5mm","C2876556","1"
"AP63200WU 5V Buck","U3","Package_TO_SOT_SMD:TSOT-23-6","C2071868","1"
"AP63200WU 3V3 Buck","U4","Package_TO_SOT_SMD:TSOT-23-6","C2071868","1"
"ADS1115IDGS 0x48","U5","Package_SO:TSSOP-10_3x3mm_P0.5mm","C37593","1"
"ADS1115IDGS 0x49","U6","Package_SO:TSSOP-10_3x3mm_P0.5mm","C37593","1"
"MCP23017-E/SO","U7","Daughterboard:SOIC-28W_7.5x17.9mm_P1.27mm_NoPads11_14","C47023","1"
"10M 1%","R49","Resistor_SMD:R_0603_1608Metric","C7250","1"
"10M 1%","R50","Resistor_SMD:R_0603_1608Metric","C7250","1"

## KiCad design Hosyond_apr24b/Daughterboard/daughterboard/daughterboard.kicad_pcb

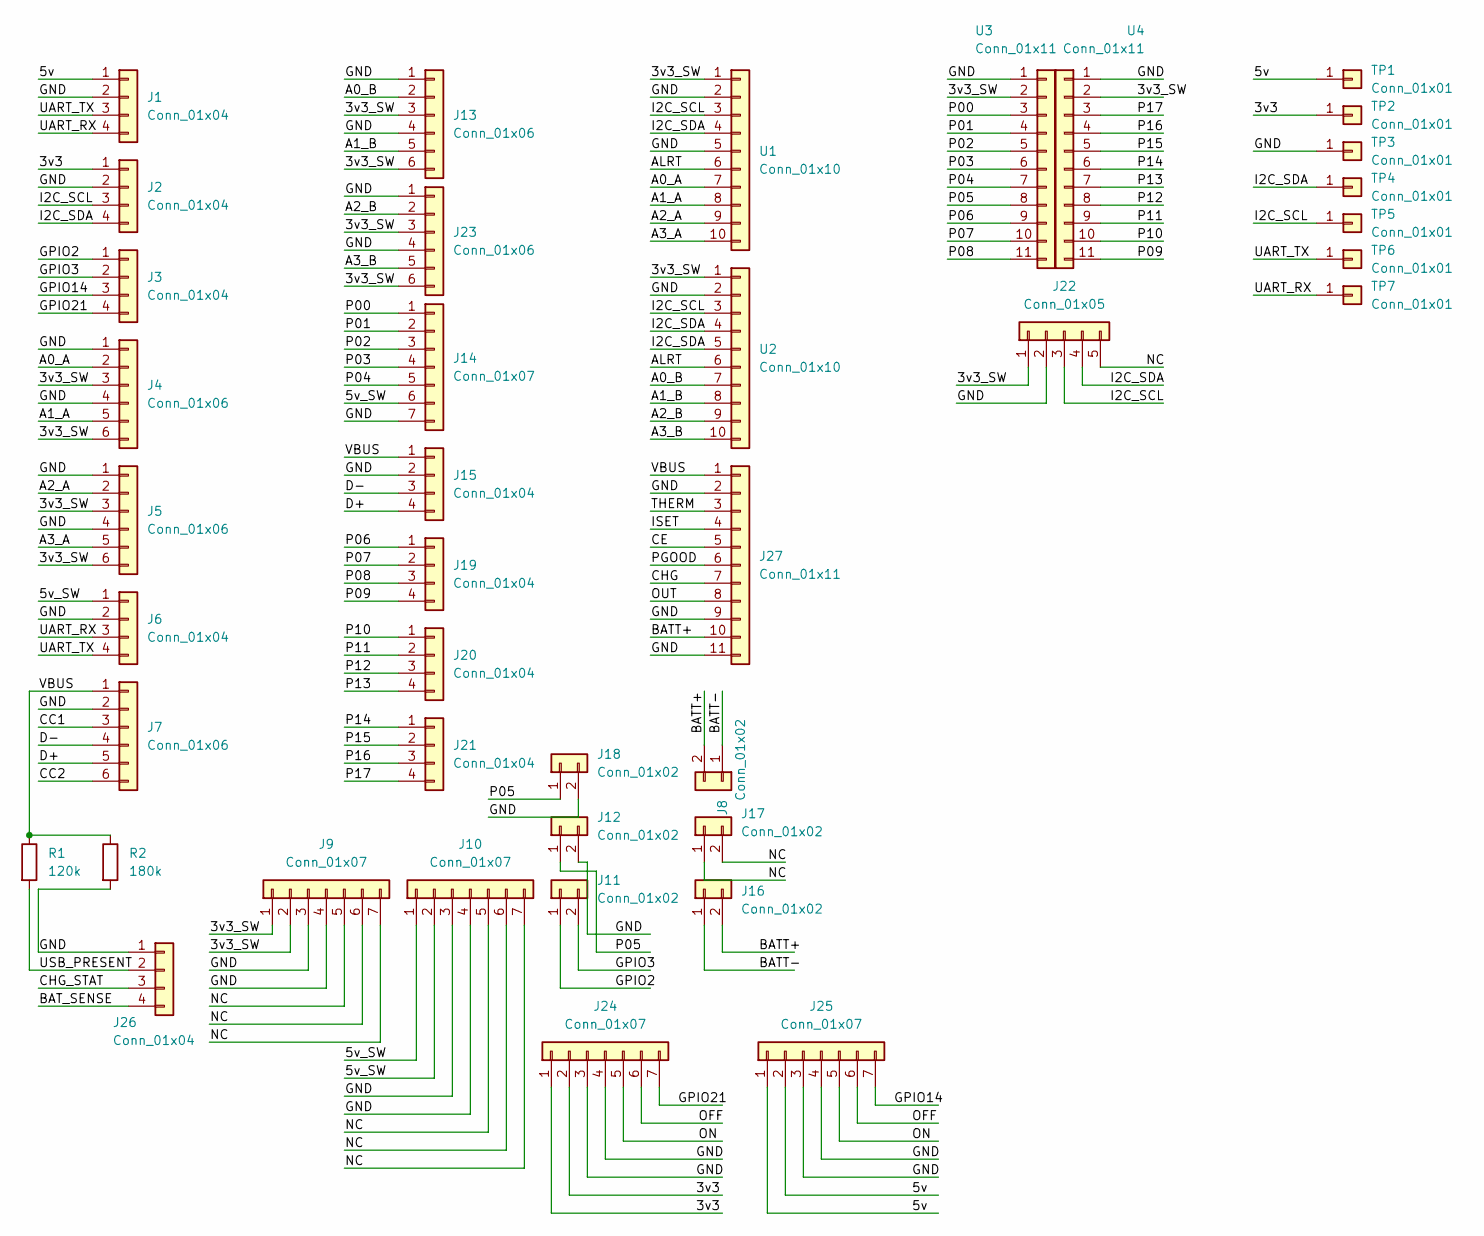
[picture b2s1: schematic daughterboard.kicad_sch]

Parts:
J1, J2, J3, J6, J19, J20, J21: Conn_01x04; PinHeader_1x04_P1.00mm_Horizontal
J4, J5, J13, J23: Conn_01x06; PinHeader_1x06_P1.00mm_Horizontal
J7: Conn_01x06; PinHeader_1x06_P2.54mm_Vertical
J8, J16: Conn_01x02; JST_PH_B2B-PH-K_1x02_P2.00mm_Vertical
J9, J10, J14, J24, J25: Conn_01x07; PinHeader_1x07_P2.54mm_Vertical
J11, J12, J18: Conn_01x02; PinHeader_1x02_P1.00mm_Horizontal
J15, J26: Conn_01x04; PinHeader_1x04_P2.54mm_Vertical
J17: Conn_01x02; PinHeader_1x02_P2.54mm_Vertical
J22: Conn_01x05; PinHeader_1x05_P2.54mm_Vertical
J27: Conn_01x11; PinHeader_1x11_P2.54mm_Vertical
R1: 120k; R_Axial_DIN0207_L6.3mm_D2.5mm_P7.62mm_Horizontal
R2: 180k; R_Axial_DIN0207_L6.3mm_D2.5mm_P7.62mm_Horizontal
TP1, TP2, TP3, TP4, TP5, TP6, TP7: Conn_01x01; TestPoint_Pad_D1.5mm
U1, U2: Conn_01x10; PinHeader_1x10_P2.54mm_Vertical
U3, U4: Conn_01x11; PinHeader_1x11_P2.54mm_Vertical

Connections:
/3v3: J2.1, J24.1, J24.2, TP2.1 (Pin_1_1)
/3v3_SW: J4.3, J4.6, J5.3, J5.6, J9.1, J9.2, J13.3, J13.6, J22.1, J23.3, J23.6, U1.1, U2.1, U3.2, U4.2
/5v: J1.1, J25.1, J25.2, TP1.1 (Pin_1_1)
/5v_SW: J6.1, J10.1, J10.2, J14.6
/A0_A: J4.2, U1.7
/A0_B: J13.2, U2.7
/A1_A: J4.5, U1.8
/A1_B: J13.5, U2.8
/A2_A: J5.2, U1.9
/A2_B: J23.2, U2.9
/A3_A: J5.5, U1.10
/A3_B: J23.5, U2.10
/ALRT: U1.6, U2.6
/BATT+: J8.2, J16.2, J27.10
/BATT-: J8.1, J16.1
/BAT_SENSE: J26.4
/CC1: J7.3
/CC2: J7.6
/CE: J27.5
/CHG: J27.7
/CHG_STAT: J26.3
/D+: J7.5, J15.4
/D-: J7.4, J15.3
/GND: J1.2, J2.2, J4.1, J4.4, J5.1, J5.4, J6.2, J7.2, J9.3, J9.4, J10.3, J10.4, J12.2, J13.1, J13.4, J14.7, J15.2, J18.2, J22.2, J23.1, J23.4, J24.3, J24.4, J25.3, J25.4, J26.1, J27.2, J27.9, J27.11, R2.2, TP3.1 (Pin_1_1), U1.2, U1.5, U2.2, U3.1, U4.1
/GPIO2: J3.1, J11.1
/GPIO3: J3.2, J11.2
/GPIO14: J3.3, J25.7
/GPIO21: J3.4, J24.7
/I2C_SCL: J2.3, J22.3, TP5.1 (Pin_1_1), U1.3, U2.3
/I2C_SDA: J2.4, J22.4, TP4.1 (Pin_1_1), U1.4, U2.4, U2.5
/ISET: J27.4
/NC: J9.5, J9.6, J9.7, J10.5, J10.6, J10.7, J17.1, J17.2, J22.5
/OFF: J24.6, J25.6
/ON: J24.5, J25.5
/OUT: J27.8
/P00: J14.1, U3.3
/P01: J14.2, U3.4
/P02: J14.3, U3.5
/P03: J14.4, U3.6
/P04: J14.5, U3.7
/P05: J12.1, J18.1, U3.8
/P06: J19.1, U3.9
/P07: J19.2, U3.10
/P08: J19.3, U3.11
/P09: J19.4, U4.11
/P10: J20.1, U4.10
/P11: J20.2, U4.9
/P12: J20.3, U4.8
/P13: J20.4, U4.7
/P14: J21.1, U4.6
/P15: J21.2, U4.5
/P16: J21.3, U4.4
/P17: J21.4, U4.3
/PGOOD: J27.6
/THERM: J27.3
/UART_RX: J1.4, J6.3, TP7.1 (Pin_1_1)
/UART_TX: J1.3, J6.4, TP6.1 (Pin_1_1)
/USB_PRESENT: J26.2, R1.2
/VBUS: J7.1, J15.1, J27.1, R1.1, R2.1

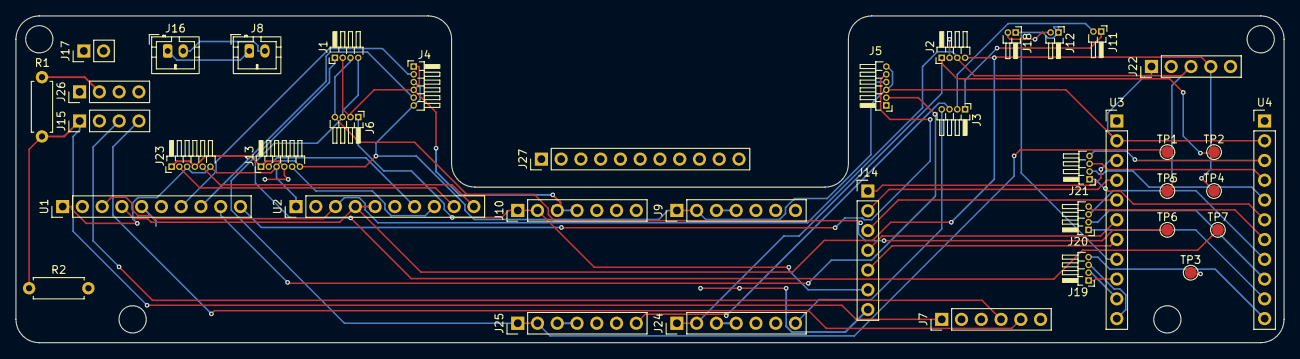
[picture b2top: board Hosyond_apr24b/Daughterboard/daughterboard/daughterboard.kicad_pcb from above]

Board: 2 copper layers, 163.0 x 42.0 mm, 40 parts (0 on the bottom side), 49 nets.

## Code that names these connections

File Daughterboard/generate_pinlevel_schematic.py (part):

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                Pin("4", "~{CE}", "L", -15.24),
                Pin("5", "EN2", "L", -10.16),
                Pin("6", "EN1", "L", -5.08),
                Pin("12", "ILIM", "L", 0),
                Pin("16", "ISET", "L", 5.08),
                Pin("14", "TMR", "L", 10.16),
                Pin("15", "ITERM", "L", 15.24),
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                Pin("6", "~{INT}", "L", -5.08, "open_collector"),
                Pin("1", "~{PG}", "L", 0, "open_collector"),
                Pin("2", "STAT", "L", 5.08, "open_collector"),
                Pin("8", "ILIM", "L", 10.16),
                Pin("15", "SNS1", "L", 15.24),
                Pin("16", "SNS2", "L", 20.32),
                Pin("7", "TS", "R", -30.48),
                Pin("10", "CBSET", "R", -25.4),
                Pin("11", "REGN", "R", -20.32, "power_out"),
                Pin("12", "BTST", "R", -15.24),
                Pin("21", "PMID1", "R", -10.16),
                Pin("22", "PMID2", "R", -5.08),
                Pin("17", "SW1", "R", 0),
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            27.94,
            35.56,
            (
                Pin("4", "AIN0", "L", -12.7),
                Pin("5", "AIN1", "L", -7.62),
                Pin("6", "AIN2", "L", -2.54),
                Pin("7", "AIN3", "L", 2.54),
                Pin("1", "ADDR", "L", 10.16),
                Pin("10", "SCL", "R", -10.16),
                Pin("9", "SDA", "R", -5.08),
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    part(two, "CREGN", "4.7uF 6.3V X5R", "Capacitor_SMD:C_0603_1608Metric", 214, 22, {"1": "REGN", "2": "GND"}, "2S charger", "REGN regulator capacitor.")
    part(two, "CBTST", "100nF 16V X7R", "Capacitor_SMD:C_0603_1608Metric", 214, 34, {"1": "BTST", "2": "CHG_SW"}, "2S charger", "Bootstrap capacitor.")
    part(two, "CCBSET", "100nF 10V X7R", "Capacitor_SMD:C_0603_1608Metric", 214, 46, {"1": "CBSET", "2": "GND"}, "2S charger", "CBSET filter placeholder; verify final requirement.")
    part(two, "CBAL1", "100nF 16V X7R", "Capacitor_SMD:C_0603_1608Metric", 214, 58, {"1": "BATT_RAW_P", "2": "CELL_MID"}, "2S charger", "Upper-cell raw-pack sense bypass; place close to charger/protection sense pins.")
    part(two, "CBAL2", "100nF 16V X7R", "Capacitor_SMD:C_0603_1608Metric", 214, 70, {"1": "CELL_MID", "2": "BATT_RAW_N"}, "2S charger", "Lower-cell raw-pack sense bypass; place close to charger/protection sense pins.")
    part(two, "NTC1", "10k NTC", "Resistor_SMD:R_0603_1608Metric", 214, 82, {"1": "TS", "2": "GND"}, "2S charger", "0603 NTC; place against or near the selected pack/cells.")
    part(two, "RTSBIAS", "10k 1%", "Resistor_SMD:R_0603_1608Metric", 214, 94, {"1": "REGN", "2": "TS"}, "2S charger", "TS bias; verify with selected NTC curve and BQ25887 TS thresholds.")
    part(two, "RSTAT_LED", "2.2k", "Resistor_SMD:R_0603_1608Metric", 254, 34, {"1": "REGN", "2": "LED_CHG_A"}, "2S charger", "Charge-status LED resistor.")
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         {"VIN": "+5V", "VOUT": "+5V_SW", "GND": "GND", "CTRL": "CTRL_5V_SW"}, "Output switching", "VIN=+5V, VOUT=+5V_SW.")
    part("POLOLU_2808", "SW2", "Pololu #2808 3V3 switch", pololu_2808_fp, 230, 270,
         {"VIN": "+3V3", "VOUT": "+3V3_SW", "GND": "GND", "CTRL": "CTRL_3V3_SW"}, "Output switching", "VIN=+3V3, VOUT=+3V3_SW.")
    part(two, "RCTRL1", "330R", "Resistor_SMD:R_0603_1608Metric", 230, 242, {"1": "GPIO2", "2": "CTRL_5V_SW"}, "Output switching", "Series resistor from ESP32 GPIO2.")
    part(two, "RCTRL2", "330R", "Resistor_SMD:R_0603_1608Metric", 230, 297, {"1": "GPIO3", "2": "CTRL_3V3_SW"}, "Output switching", "Series resistor from ESP32 GPIO3.")
    hosyond_pad_fp = "TestPoint:TestPoint_Pad_1.5x1.5mm"
    hosyond_pads = [
        ("J30", "J3P", "+5V_SW", 295, 188),
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        ("J32", "J3B", "UART_RX", 295, 208),
        ("J33", "J3C", "I2C_SDA", 295, 218),
        ("J34", "J3D", "I2C_SCL", 295, 228),
        ("J35", "J3E", "GPIO2", 295, 238),
        ("J36", "J3F", "GPIO3", 295, 248),
        ("J37", "J3G", "GPIO14", 295, 258),
        ("J38", "J3H", "GPIO21", 295, 268),
        ("J39", "J3I", "GND", 295, 278),
    ]
    for ref, pad_name, net, x, y in hosyond_pads:
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         {"1": "+3V3_SW", "2": "GND", "3": "I2C_SDA", "4": "I2C_SCL"},
         "Signals", "4-pin 2.54mm I2C header: +3V3_SW,GND,SDA,SCL.")
    part("CONN_2", "J6", "Deep sleep pushbutton header", "Connector_PinHeader_2.54mm:PinHeader_1x02_P2.54mm_Vertical", 390, 265,
         {"1": "GPIO14", "2": "GPIO21"},
         "Signals", "2-pin 2.54mm header for pushbutton between GPIO14 and GPIO21.")

    part("ADS1115IDGS", "U5", "ADS1115IDGS 0x48", "Package_SO:TSSOP-10_3x3mm_P0.5mm", 360, 52,
         {"AIN0": "AIN0", "AIN1": "AIN1", "AIN2": "AIN2", "AIN3": "AIN3", "ADDR": "GND",
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    part(two, "C28", "1uF 10V X5R", "Capacitor_SMD:C_0603_1608Metric", 262, 257,
         {"1": "+3V3_SW_LOGIC", "2": "GND"}, "GPIO expander", "MCP23017 local supply bulk.")
    part(two, "R39", "0R", "Resistor_SMD:R_0603_1608Metric", 262, 269,
         {"1": "MCP_A0", "2": "GND"}, "GPIO expander", "Default address strap low; A2:A0=000 gives I2C address 0x20.")
    part(two, "R40", "0R", "Resistor_SMD:R_0603_1608Metric", 262, 281,
         {"1": "MCP_A1", "2": "GND"}, "GPIO expander", "Default address strap low.")
    part(two, "R41", "0R", "Resistor_SMD:R_0603_1608Metric", 262, 293,
         {"1": "MCP_A2", "2": "GND"}, "GPIO expander", "Default address strap low.")
    part(two, "R42", "10k", "Resistor_SMD:R_0603_1608Metric", 262, 305,
         {"1": "+3V3_SW_LOGIC", "2": "MCP_RESET"}, "GPIO expander", "Reset pullup to switched 3.3V logic branch.")
    part(two, "C29", "100nF 10V X7R", "Capacitor_SMD:C_0603_1608Metric", 262, 317,
         {"1": "MCP_RESET", "2": "GND"}, "GPIO expander", "Optional reset delay/noise filter; omit if firmware needs immediate reset release.")
    part(two, "R43", "10k", "Resistor_SMD:R_0603_1608Metric", 332, 245,
         {"1": "+3V3_SW_LOGIC", "2": "MCP_INTA"}, "GPIO expander", "INTA pullup; also available on a solder pad.")
    part(two, "R44", "10k", "Resistor_SMD:R_0603_1608Metric", 332, 257,
         {"1": "+3V3_SW_LOGIC", "2": "MCP_INTB"}, "GPIO expander", "INTB pullup; also available on a solder pad.")

    gpio_series = [
        ("R23", "MCP_GPA0", "EXP_GPA0", 390, 285), ("R24", "MCP_GPA1", "EXP_GPA1", 390, 297),
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
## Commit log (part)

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2026-06-29 a
    a
